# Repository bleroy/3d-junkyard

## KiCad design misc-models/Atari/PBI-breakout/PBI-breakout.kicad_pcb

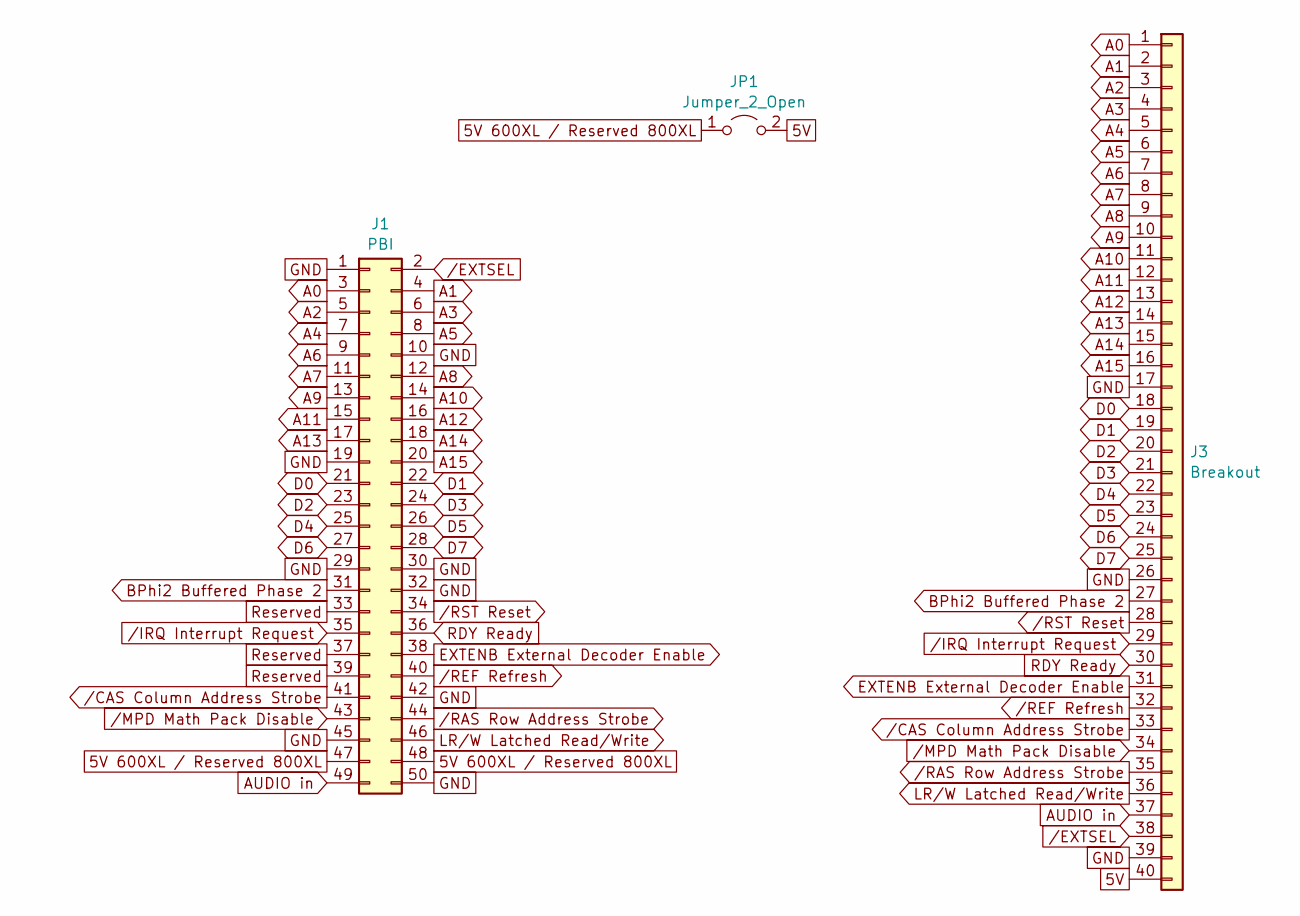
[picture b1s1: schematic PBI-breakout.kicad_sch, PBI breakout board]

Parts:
J1: PBI; PBI Edge Connector
J3: Breakout; PinHeader_1x40_P2.54mm_Horizontal
JP1: Jumper_2_Open; PinHeader_1x02_P2.54mm_Vertical

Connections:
5V: J3.40, JP1.2 (B)
5V 600XL / Reserved 800XL: J1.47, J1.48, JP1.1 (A)
A0: J1.3, J3.1
A1: J1.4, J3.2
A2: J1.5, J3.3
A3: J1.6, J3.4
A4: J1.7, J3.5
A5: J1.8, J3.6
A6: J1.9, J3.7
A7: J1.11, J3.8
A8: J1.12, J3.9
A9: J1.13, J3.10
A10: J1.14, J3.11
A11: J1.15, J3.12
A12: J1.16, J3.13
A13: J1.17, J3.14
A14: J1.18, J3.15
A15: J1.20, J3.16
AUDIO in: J1.49, J3.37
BPhi2 Buffered Phase 2: J1.31, J3.27
D0: J1.21, J3.18
D1: J1.22, J3.19
D2: J1.23, J3.20
D3: J1.24, J3.21
D4: J1.25, J3.22
D5: J1.26, J3.23
D6: J1.27, J3.24
D7: J1.28, J3.25
EXTENB External Decoder Enable: J1.38, J3.31
GND: J1.1, J1.10, J1.19, J1.29, J1.30, J1.32, J1.42, J1.45, J1.50, J3.17, J3.26, J3.39
LR/W Latched Read/Write: J1.46, J3.36
RDY Ready: J1.36, J3.30
Reserved: J1.33, J1.37, J1.39
/CAS Column Address Strobe: J1.41, J3.33
/EXTSEL: J1.2, J3.38
/IRQ Interrupt Request: J1.35, J3.29
/MPD Math Pack Disable: J1.43, J3.34
/RAS Row Address Strobe: J1.44, J3.35
/REF Refresh: J1.40, J3.32
/RST Reset: J1.34, J3.28

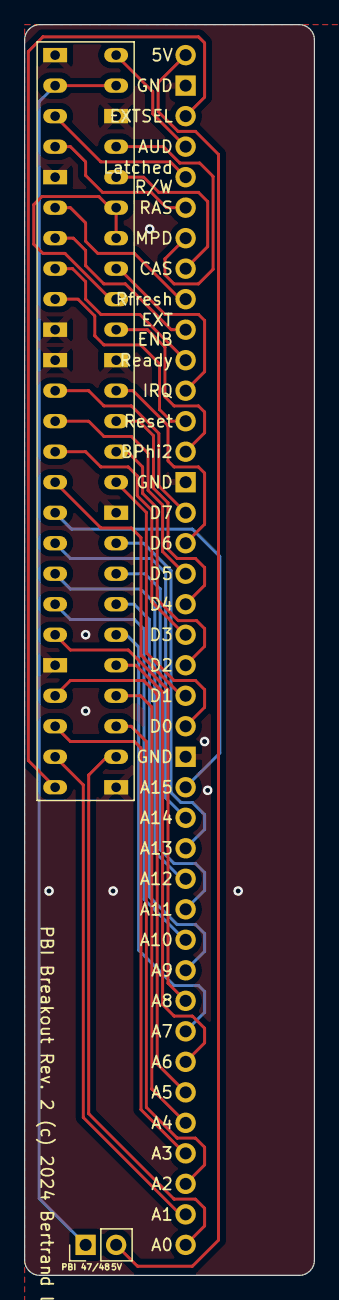
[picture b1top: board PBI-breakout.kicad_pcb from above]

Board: 2 copper layers, 24.1 x 104.1 mm, 3 parts (1 on the bottom side), 40 nets.

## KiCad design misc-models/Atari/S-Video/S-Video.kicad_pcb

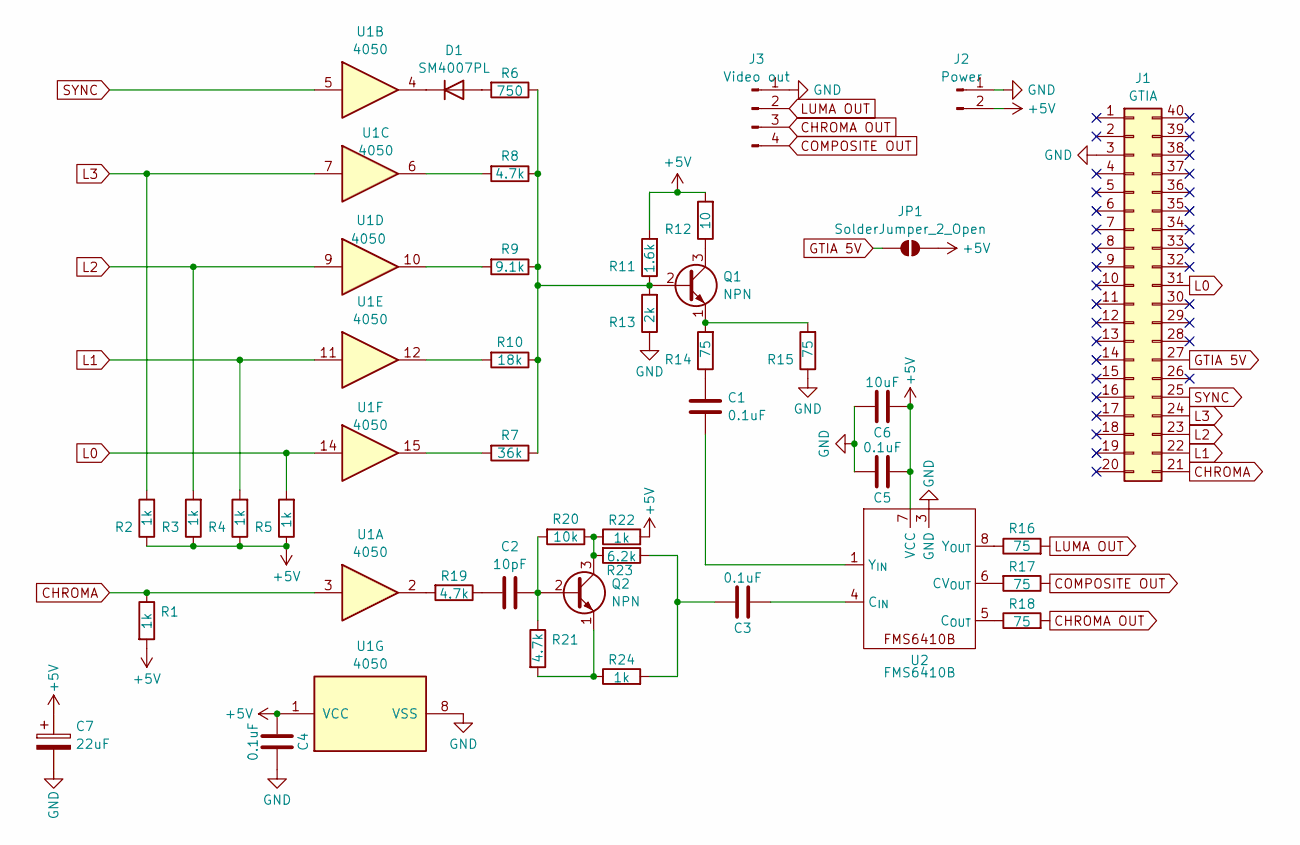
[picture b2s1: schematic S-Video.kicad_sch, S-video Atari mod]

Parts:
C1, C3, C4, C5: 0.1uF; C_0402_1005Metric; JLCPCB Part # C1525
C2: 10pF; C_0402_1005Metric; JLCPCB Part # C32949
C6: 10uF; C_0402_1005Metric; JLCPCB Part # C15525
C7: 22uF; C_Elec_4x5.4; JLCPCB Part # C98746
D1: SM4007PL; D_SOD-123; JLCPCB Part # C64898
J1: GTIA; DIP-40_W15.24mm_Socket
J2: Power; PinHeader_1x02_P2.54mm_Horizontal
J3: Video out; PinHeader_1x04_P2.54mm_Horizontal
JP1: SolderJumper_2_Open; SolderJumper-2_P1.3mm_Open_TrianglePad1.0x1.5mm
Q1, Q2: NPN; SOT-23; JLCPCB Part # C2145
R1, R2, R3, R4, R5, R22, R24: 1k; R_0402_1005Metric; JLCPCB Part # C11702
R6: 750; R_0402_1005Metric; JLCPCB Part # C25132
R7: 36k; R_0402_1005Metric; JLCPCB Part # C43676
R8, R19, R21: 4.7k; R_0402_1005Metric; JLCPCB Part # C25900
R9: 9.1k; R_0402_1005Metric; JLCPCB Part # C25926
R10: 18k; R_0402_1005Metric; JLCPCB Part # C25762
R11: 1.6k; R_0402_1005Metric; JLCPCB Part # C4908
R12: 10; R_0402_1005Metric; JLCPCB Part # C25077
R13: 2k; R_0402_1005Metric; JLCPCB Part # C4109
R14, R15, R16, R17, R18: 75; R_0402_1005Metric; JLCPCB Part # C25133
R20: 10k; R_0402_1005Metric; JLCPCB Part # C25744
R23: 6.2k; R_0402_1005Metric; JLCPCB Part # C137946
U1: 4050; SOIC-16_3.9x9.9mm_P1.27mm; JLCPCB Part # C131932
U2: FMS6410B; SOIC-8-1EP_3.9x4.9mm_P1.27mm_EP2.29x3mm; JLCPCB Part # C3823926

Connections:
+5V: C4.1, C5.1, C6.1, C7.1, J2.2, JP1.2 (B), R1.2, R2.1, R3.1, R4.1, R5.1, R11.2, R12.2, R22.2, U1.1 (VCC), U2.7 (VCC)
CHROMA: J1.21, R1.1, U1.3
CHROMA OUT: J3.3, R18.2
COMPOSITE OUT: J3.4, R17.1
GND: C4.2, C5.2, C6.2, C7.2, J1.3, J2.1, J3.1, R13.1, R15.1, U1.8 (VSS), U2.3 (GND)
GTIA 5V: J1.27, JP1.1 (A)
L0: J1.31, R5.2, U1.14
L1: J1.22, R4.2, U1.11
L2: J1.23, R3.2, U1.9
L3: J1.24, R2.2, U1.7
LUMA OUT: J3.2, R16.2
unnamed: C1.2, R14.1
unnamed: C2.2, R19.1
unnamed: C3.2, R23.1, R24.2
unnamed: D1.2 (A), R6.2
unnamed: D1.1 (K), U1.4
unnamed: Q1.2 (B), R6.1, R7.1, R8.1, R9.1, R10.1, R11.1, R13.2
unnamed: Q1.3 (C), R12.1
unnamed: Q1.1 (E), R14.2, R15.2
unnamed: C2.1, Q2.2 (B), R20.2, R21.1
unnamed: Q2.3 (C), R20.1, R22.1, R23.2
unnamed: Q2.1 (E), R21.2, R24.1
unnamed: R7.2, U1.15
unnamed: R8.2, U1.6
unnamed: R9.2, U1.10
unnamed: R10.2, U1.12
unnamed: R19.2, U1.2
unnamed: R17.2, U2.6 (CV_{OUT})
unnamed: C3.1, U2.4 (C_{IN})
unnamed: R18.1, U2.5 (C_{OUT})
unnamed: C1.1, U2.1 (Y_{IN})
unnamed: R16.1, U2.8 (Y_{OUT})
SYNC: J1.25, U1.5

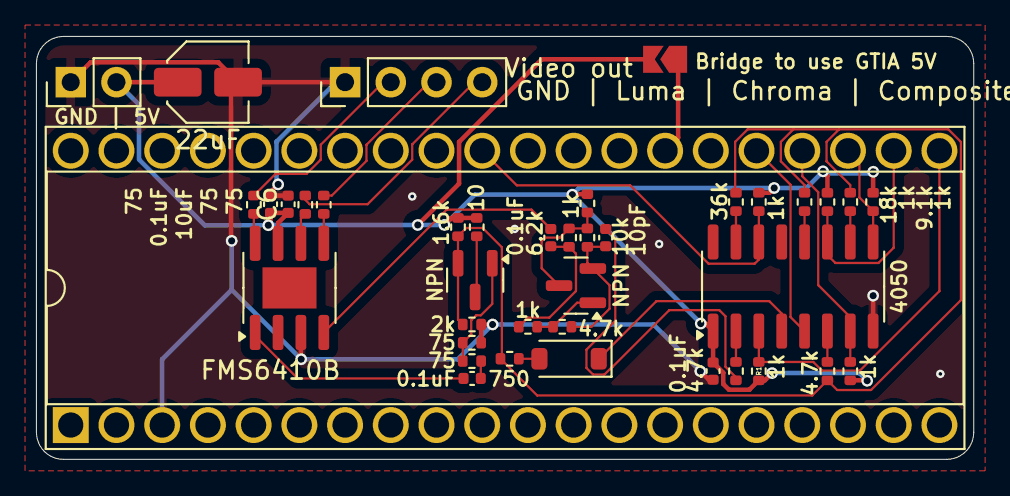
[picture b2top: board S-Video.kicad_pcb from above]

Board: 2 copper layers, 52.1 x 23.5 mm, 40 parts (0 on the bottom side), 33 nets.

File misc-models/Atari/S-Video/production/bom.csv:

Designator,Footprint,Quantity,Value,LCSC Part #
"C1, C3, C4, C5",0402,4,0.1uF,C1525
C2,0402,1,10pF,C32949
C6,0402,1,10uF,C15525
C7,C_Elec_4x5.4,1,22uF,C98746
D1,D_SOD-123,1,SM4007PL,C64898
J1,DIP-40_W15.24mm_Socket,1,GTIA,
J2,PinHeader_1x02_P2.54mm_Vertical,1,Power,
J3,PinHeader_1x04_P2.54mm_Vertical,1,Video out,
"Q1, Q2",SOT-23,2,NPN,C2145
"R1, R2, R22, R24, R3, R4, R5",0402,7,1k,C11702
R10,0402,1,18k,C25762
R11,0402,1,1.6k,C4908
R12,0402,1,10,C25077
R13,0402,1,2k,C4109
"R14, R15, R16, R17, R18",0402,5,75,C25133
"R19, R21, R8",0402,3,4.7k,C25900
R20,0402,1,10k,C25744
R23,0402,1,6.2k,C137946
R6,0402,1,750,C25132
R7,0402,1,36k,C43676
R9,0402,1,9.1k,C25926
U1,SOIC-16_3.9x9.9mm_P1.27mm,1,4050,C131932
U2,SOIC-8-1EP_3.9x4.9mm_P1.27mm_EP2.29x3mm,1,FMS6410B,C3823926

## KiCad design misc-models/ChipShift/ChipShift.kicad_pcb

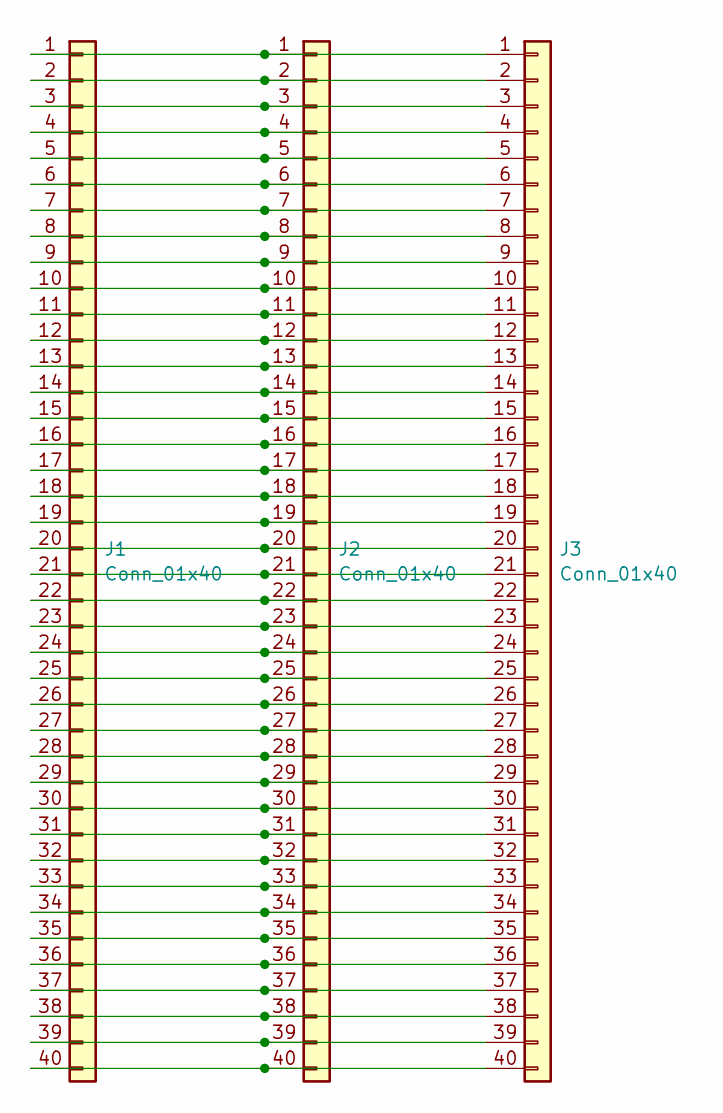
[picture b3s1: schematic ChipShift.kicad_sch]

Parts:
J1, J2: Conn_01x40; DIP-40_W25.4mm
J3: Conn_01x40; IDC-Header_2x20_P2.54mm_Vertical

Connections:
unnamed: J1.1, J2.1, J3.1
unnamed: J1.2, J2.2, J3.2
unnamed: J1.3, J2.3, J3.3
unnamed: J1.4, J2.4, J3.4
unnamed: J1.5, J2.5, J3.5
unnamed: J1.6, J2.6, J3.6
unnamed: J1.7, J2.7, J3.7
unnamed: J1.8, J2.8, J3.8
unnamed: J1.9, J2.9, J3.9
unnamed: J1.10, J2.10, J3.10
unnamed: J1.11, J2.11, J3.11
unnamed: J1.12, J2.12, J3.12
unnamed: J1.13, J2.13, J3.13
unnamed: J1.14, J2.14, J3.14
unnamed: J1.15, J2.15, J3.15
unnamed: J1.16, J2.16, J3.16
unnamed: J1.17, J2.17, J3.17
unnamed: J1.18, J2.18, J3.18
unnamed: J1.19, J2.19, J3.19
unnamed: J1.20, J2.20, J3.20
unnamed: J1.21, J2.21, J3.21
unnamed: J1.22, J2.22, J3.22
unnamed: J1.23, J2.23, J3.23
unnamed: J1.24, J2.24, J3.24
unnamed: J1.25, J2.25, J3.25
unnamed: J1.26, J2.26, J3.26
unnamed: J1.27, J2.27, J3.27
unnamed: J1.28, J2.28, J3.28
unnamed: J1.29, J2.29, J3.29
unnamed: J1.30, J2.30, J3.30
unnamed: J1.31, J2.31, J3.31
unnamed: J1.32, J2.32, J3.32
unnamed: J1.33, J2.33, J3.33
unnamed: J1.34, J2.34, J3.34
unnamed: J1.35, J2.35, J3.35
unnamed: J1.36, J2.36, J3.36
unnamed: J1.37, J2.37, J3.37
unnamed: J1.38, J2.38, J3.38
unnamed: J1.39, J2.39, J3.39
unnamed: J1.40, J2.40, J3.40

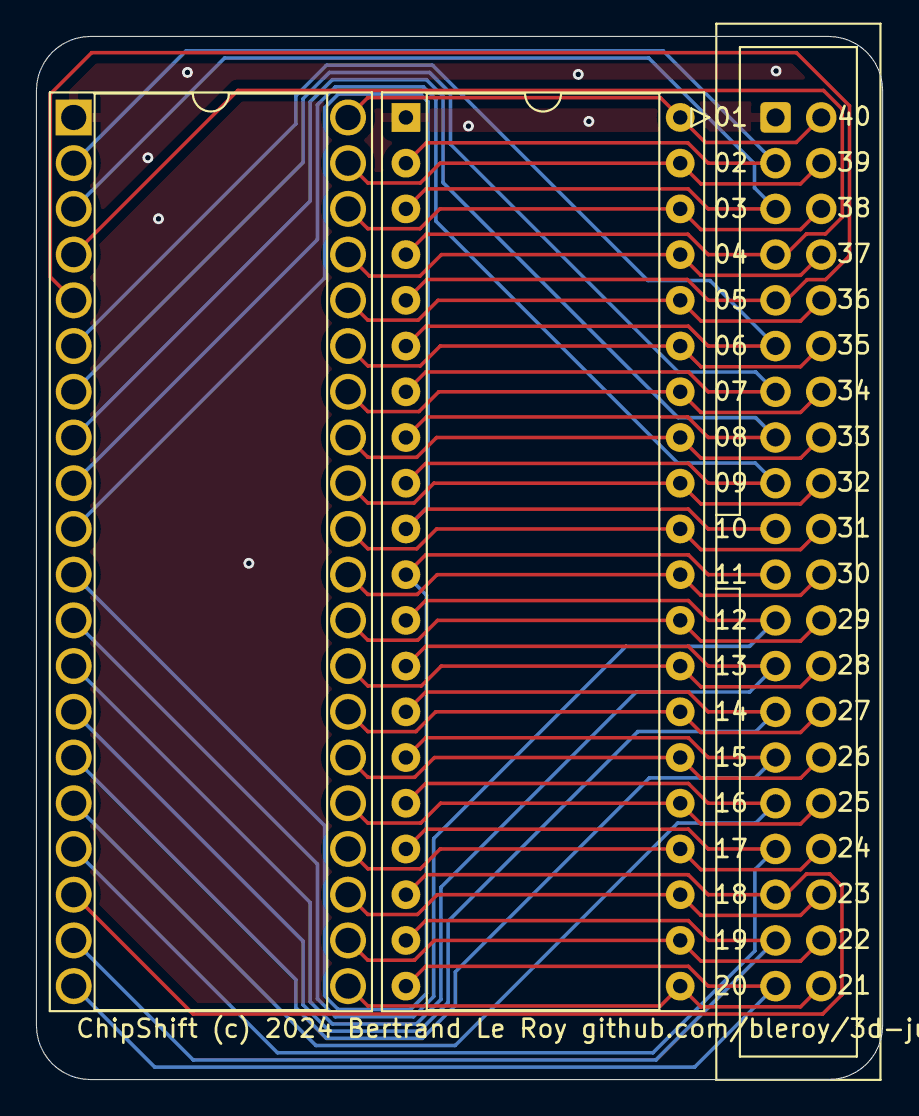
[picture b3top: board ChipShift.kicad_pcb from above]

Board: 2 copper layers, 47.0 x 58.0 mm, 3 parts (0 on the bottom side), 40 nets.

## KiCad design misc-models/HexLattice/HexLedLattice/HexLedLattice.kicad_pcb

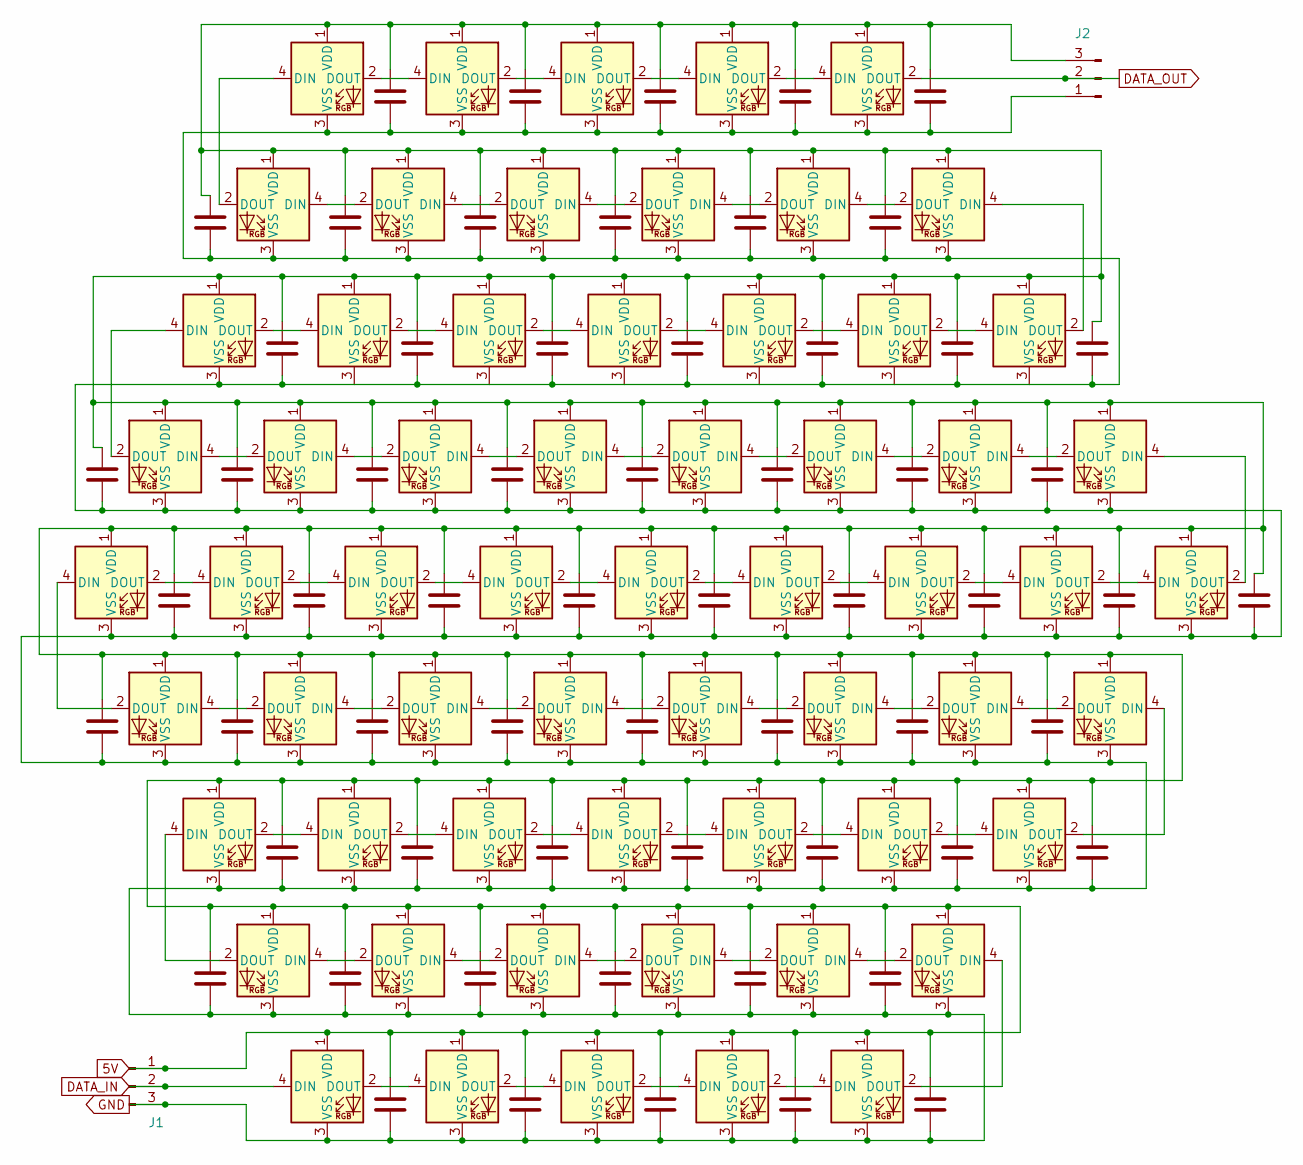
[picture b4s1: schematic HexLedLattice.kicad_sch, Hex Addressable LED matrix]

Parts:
C1, C2, C3, C4, C5, C6, C7, C8, C9, C10, C11, C12, C13, C14, C15, C16, C17, C18, C19, C20, C21, C22, C23, C24, C25, C26, C27, C28, C29, C30, C31, C32, C33, C34, C35, C36, C37, C38, C39, C40, C41, C42, C43, C44, C45, C46, C47, C48, C49, C50, C51, C52, C53, C54, C55, C56, C57, C58, C59, C60, C61: C; C_0201_0603Metric
D1, D2, D3, D4, D5, D6, D7, D8, D9, D10, D11, D12, D13, D14, D15, D16, D17, D18, D19, D20, D21, D22, D23, D24, D25, D26, D27, D28, D29, D30, D31, D32, D33, D34, D35, D36, D37, D38, D39, D40, D41, D42, D43, D44, D45, D46, D47, D48, D49, D50, D51, D52, D53, D54, D55, D56, D57, D58, D59, D60, D61: WS2812B; LED_WS2812B_PLCC4_5.0x5.0mm_P3.2mm
J1, J2: Conn_01x03_Pin; Connector_1x04-1MP_P1.0mm_Horizontal

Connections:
5V: C1.1, C2.1, C3.1, C4.1, C5.1, C6.1, C7.1, C8.1, C9.1, C10.1, C11.1, C12.1, C13.1, C14.1, C15.1, C16.1, C17.1, C18.1, C19.1, C20.1, C21.1, C22.1, C23.1, C24.1, C25.1, C26.1, C27.1, C28.1, C29.1, C30.1, C31.1, C32.1, C33.1, C34.1, C35.1, C36.1, C37.1, C38.1, C39.1, C40.1, C41.1, C42.1, C43.1, C44.1, C45.1, C46.1, C47.1, C48.1, C49.1, C50.1, C51.1, C52.1, C53.1, C54.1, C55.1, C56.1, C57.1, C58.1, C59.1, C60.1, C61.1, D1.1 (VDD), D2.1 (VDD), D3.1 (VDD), D4.1 (VDD), D5.1 (VDD), D6.1 (VDD), D7.1 (VDD), D8.1 (VDD), D9.1 (VDD), D10.1 (VDD), D11.1 (VDD), D12.1 (VDD), D13.1 (VDD), D14.1 (VDD), D15.1 (VDD), D16.1 (VDD), D17.1 (VDD), D18.1 (VDD), D19.1 (VDD), D20.1 (VDD), D21.1 (VDD), D22.1 (VDD), D23.1 (VDD), D24.1 (VDD), D25.1 (VDD), D26.1 (VDD), D27.1 (VDD), D28.1 (VDD), D29.1 (VDD), D30.1 (VDD), D31.1 (VDD), D32.1 (VDD), D33.1 (VDD), D34.1 (VDD), D35.1 (VDD), D36.1 (VDD), D37.1 (VDD), D38.1 (VDD), D39.1 (VDD), D40.1 (VDD), D41.1 (VDD), D42.1 (VDD), D43.1 (VDD), D44.1 (VDD), D45.1 (VDD), D46.1 (VDD), D47.1 (VDD), D48.1 (VDD), D49.1 (VDD), D50.1 (VDD), D51.1 (VDD), D52.1 (VDD), D53.1 (VDD), D54.1 (VDD), D55.1 (VDD), D56.1 (VDD), D57.1 (VDD), D58.1 (VDD), D59.1 (VDD), D60.1 (VDD), D61.1 (VDD), J1.1, J2.3
DATA_IN: D40.4 (DIN), J1.2
DATA_OUT: D5.2 (DOUT), J2.2
GND: C1.2, C2.2, C3.2, C4.2, C5.2, C6.2, C7.2, C8.2, C9.2, C10.2, C11.2, C12.2, C13.2, C14.2, C15.2, C16.2, C17.2, C18.2, C19.2, C20.2, C21.2, C22.2, C23.2, C24.2, C25.2, C26.2, C27.2, C28.2, C29.2, C30.2, C31.2, C32.2, C33.2, C34.2, C35.2, C36.2, C37.2, C38.2, C39.2, C40.2, C41.2, C42.2, C43.2, C44.2, C45.2, C46.2, C47.2, C48.2, C49.2, C50.2, C51.2, C52.2, C53.2, C54.2, C55.2, C56.2, C57.2, C58.2, C59.2, C60.2, C61.2, D1.3 (VSS), D2.3 (VSS), D3.3 (VSS), D4.3 (VSS), D5.3 (VSS), D6.3 (VSS), D7.3 (VSS), D8.3 (VSS), D9.3 (VSS), D10.3 (VSS), D11.3 (VSS), D12.3 (VSS), D13.3 (VSS), D14.3 (VSS), D15.3 (VSS), D16.3 (VSS), D17.3 (VSS), D18.3 (VSS), D19.3 (VSS), D20.3 (VSS), D21.3 (VSS), D22.3 (VSS), D23.3 (VSS), D24.3 (VSS), D25.3 (VSS), D26.3 (VSS), D27.3 (VSS), D28.3 (VSS), D29.3 (VSS), D30.3 (VSS), D31.3 (VSS), D32.3 (VSS), D33.3 (VSS), D34.3 (VSS), D35.3 (VSS), D36.3 (VSS), D37.3 (VSS), D38.3 (VSS), D39.3 (VSS), D40.3 (VSS), D41.3 (VSS), D42.3 (VSS), D43.3 (VSS), D44.3 (VSS), D45.3 (VSS), D46.3 (VSS), D47.3 (VSS), D48.3 (VSS), D49.3 (VSS), D50.3 (VSS), D51.3 (VSS), D52.3 (VSS), D53.3 (VSS), D54.3 (VSS), D55.3 (VSS), D56.3 (VSS), D57.3 (VSS), D58.3 (VSS), D59.3 (VSS), D60.3 (VSS), D61.3 (VSS), J1.3, J2.1
unnamed: D1.4 (DIN), D11.2 (DOUT)
unnamed: D1.2 (DOUT), D2.4 (DIN)
unnamed: D2.2 (DOUT), D3.4 (DIN)
unnamed: D3.2 (DOUT), D4.4 (DIN)
unnamed: D4.2 (DOUT), D5.4 (DIN)
unnamed: D6.2 (DOUT), D7.4 (DIN)
unnamed: D7.2 (DOUT), D8.4 (DIN)
unnamed: D8.2 (DOUT), D9.4 (DIN)
unnamed: D9.2 (DOUT), D10.4 (DIN)
unnamed: D10.2 (DOUT), D11.4 (DIN)
unnamed: D12.4 (DIN), D26.2 (DOUT)
unnamed: D12.2 (DOUT), D13.4 (DIN)
unnamed: D13.2 (DOUT), D14.4 (DIN)
unnamed: D14.2 (DOUT), D15.4 (DIN)
unnamed: D15.2 (DOUT), D16.4 (DIN)
unnamed: D16.2 (DOUT), D17.4 (DIN)
unnamed: D17.2 (DOUT), D18.4 (DIN)
unnamed: D6.4 (DIN), D18.2 (DOUT)
unnamed: D19.4 (DIN), D52.2 (DOUT)
unnamed: D19.2 (DOUT), D20.4 (DIN)
unnamed: D20.2 (DOUT), D21.4 (DIN)
unnamed: D21.2 (DOUT), D22.4 (DIN)
unnamed: D22.2 (DOUT), D23.4 (DIN)
unnamed: D23.2 (DOUT), D24.4 (DIN)
unnamed: D24.2 (DOUT), D25.4 (DIN)
unnamed: D25.2 (DOUT), D26.4 (DIN)
unnamed: D27.4 (DIN), D39.2 (DOUT)
unnamed: D27.2 (DOUT), D28.4 (DIN)
unnamed: D28.2 (DOUT), D29.4 (DIN)
unnamed: D29.2 (DOUT), D30.4 (DIN)
unnamed: D30.2 (DOUT), D31.4 (DIN)
unnamed: D31.2 (DOUT), D32.4 (DIN)
unnamed: D32.2 (DOUT), D33.4 (DIN)
unnamed: D33.2 (DOUT), D54.4 (DIN)
unnamed: D34.4 (DIN), D44.2 (DOUT)
unnamed: D34.2 (DOUT), D35.4 (DIN)
unnamed: D35.2 (DOUT), D36.4 (DIN)
unnamed: D36.2 (DOUT), D37.4 (DIN)
unnamed: D37.2 (DOUT), D38.4 (DIN)
unnamed: D38.2 (DOUT), D39.4 (DIN)
unnamed: D40.2 (DOUT), D41.4 (DIN)
unnamed: D41.2 (DOUT), D42.4 (DIN)
unnamed: D42.2 (DOUT), D43.4 (DIN)
unnamed: D43.2 (DOUT), D44.4 (DIN)
unnamed: D45.4 (DIN), D53.2 (DOUT)
unnamed: D45.2 (DOUT), D46.4 (DIN)
unnamed: D46.2 (DOUT), D47.4 (DIN)
unnamed: D47.2 (DOUT), D48.4 (DIN)
unnamed: D48.2 (DOUT), D49.4 (DIN)
unnamed: D49.2 (DOUT), D50.4 (DIN)
unnamed: D50.2 (DOUT), D51.4 (DIN)
unnamed: D51.2 (DOUT), D52.4 (DIN)
unnamed: D53.4 (DIN), D61.2 (DOUT)
unnamed: D54.2 (DOUT), D55.4 (DIN)
unnamed: D55.2 (DOUT), D56.4 (DIN)
unnamed: D56.2 (DOUT), D57.4 (DIN)
unnamed: D57.2 (DOUT), D58.4 (DIN)
unnamed: D58.2 (DOUT), D59.4 (DIN)
unnamed: D59.2 (DOUT), D60.4 (DIN)
unnamed: D60.2 (DOUT), D61.4 (DIN)

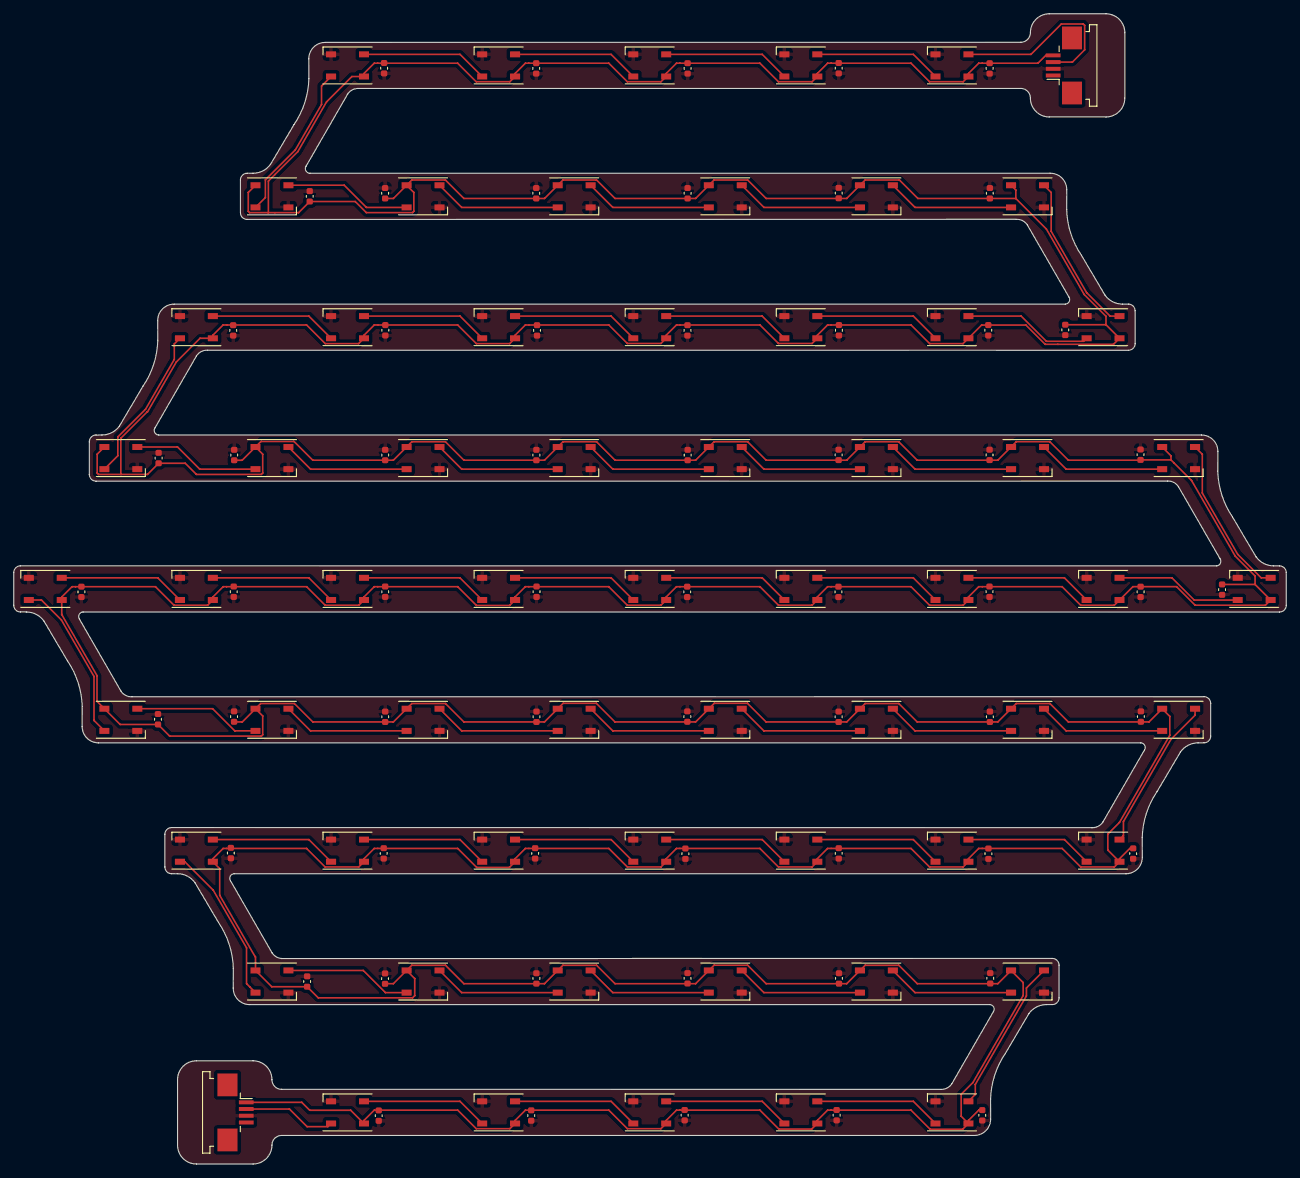
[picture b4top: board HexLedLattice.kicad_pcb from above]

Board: 2 copper layers, 189.5 x 171.3 mm, 124 parts (0 on the bottom side), 64 nets.

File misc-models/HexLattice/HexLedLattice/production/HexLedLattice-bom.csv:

Designator,Footprint,Quantity,Value,LCSC Part #
"C1, C10, C11, C12, C13, C14, C15, C16, C17, C18, C19, C2, C20, C21, C22, C23, C24, C25, C26, C27, C28, C29, C3, C30, C31, C32, C33, C34, C35, C36, C37, C38, C39, C4, C40, C41, C42, C43, C44, C45, C46, C47, C48, C49, C5, C50, C51, C52, C53, C54, C55, C56, C57, C58, C59, C6, C60, C61, C7, C8, C9",0603,61,C,
"D1, D10, D11, D12, D13, D14, D15, D16, D17, D18, D19, D2, D20, D21, D22, D23, D24, D25, D26, D27, D28, D29, D3, D30, D31, D32, D33, D34, D35, D36, D37, D38, D39, D4, D40, D41, D42, D43, D44, D45, D46, D47, D48, D49, D5, D50, D51, D52, D53, D54, D55, D56, D57, D58, D59, D6, D60, D61, D7, D8, D9",LED_WS2812B_PLCC4_5.0x5.0mm_P3.2mm,61,WS2812B,
"J1, J2",Connector_1x04-1MP_P1.0mm_Horizontal,2,Conn_01x03_Pin,

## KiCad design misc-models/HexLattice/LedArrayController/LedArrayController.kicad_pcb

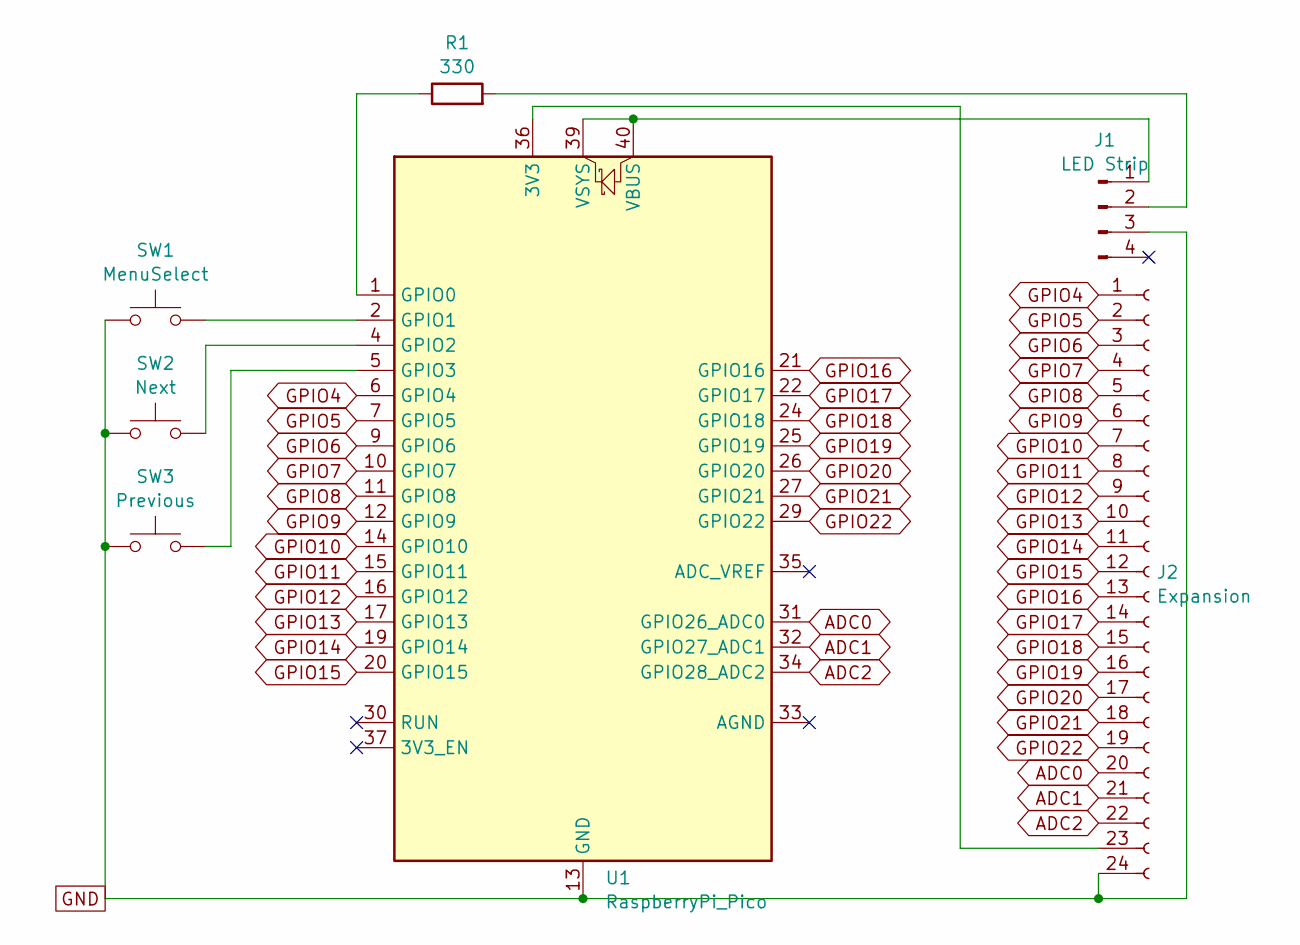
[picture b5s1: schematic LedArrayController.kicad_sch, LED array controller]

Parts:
J1: LED Strip; Connector_1x04-1MP_P1.0mm_Horizontal
J2: Expansion; PinSocket_1x24_P2.54mm_Horizontal
R1: 330; R_Axial_DIN0207_L6.3mm_D2.5mm_P7.62mm_Horizontal
SW1: MenuSelect; SW_PUSH_6mm
SW2: Next; SW_PUSH_6mm
SW3: Previous; SW_PUSH_6mm
U1: RaspberryPi_Pico; RaspberryPi_Pico_W_SMD_MountingHoles_Castellated_HandSolder

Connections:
ADC0: J2.20, U1.31 (GPIO26_ADC0)
ADC1: J2.21, U1.32 (GPIO27_ADC1)
ADC2: J2.22, U1.34 (GPIO28_ADC2)
GND: J1.3, J2.24, SW1.1, SW2.1, SW3.1, U1.3 (GND), U1.8 (GND), U1.13 (GND), U1.18 (GND), U1.23 (GND), U1.28 (GND), U1.38 (GND)
GPIO4: J2.1, U1.6 (GPIO4)
GPIO5: J2.2, U1.7 (GPIO5)
GPIO6: J2.3, U1.9 (GPIO6)
GPIO7: J2.4, U1.10 (GPIO7)
GPIO8: J2.5, U1.11 (GPIO8)
GPIO9: J2.6, U1.12 (GPIO9)
GPIO10: J2.7, U1.14 (GPIO10)
GPIO11: J2.8, U1.15 (GPIO11)
GPIO12: J2.9, U1.16 (GPIO12)
GPIO13: J2.10, U1.17 (GPIO13)
GPIO14: J2.11, U1.19 (GPIO14)
GPIO15: J2.12, U1.20 (GPIO15)
GPIO16: J2.13, U1.21 (GPIO16)
GPIO17: J2.14, U1.22 (GPIO17)
GPIO18: J2.15, U1.24 (GPIO18)
GPIO19: J2.16, U1.25 (GPIO19)
GPIO20: J2.17, U1.26 (GPIO20)
GPIO21: J2.18, U1.27 (GPIO21)
GPIO22: J2.19, U1.29 (GPIO22)
unnamed: J1.1, U1.39 (VSYS), U1.40 (VBUS)
unnamed: J1.2, R1.2
unnamed: J2.23, U1.36 (3V3)
unnamed: R1.1, U1.1 (GPIO0)
unnamed: SW1.2, U1.2 (GPIO1)
unnamed: SW2.2, U1.4 (GPIO2)
unnamed: SW3.2, U1.5 (GPIO3)

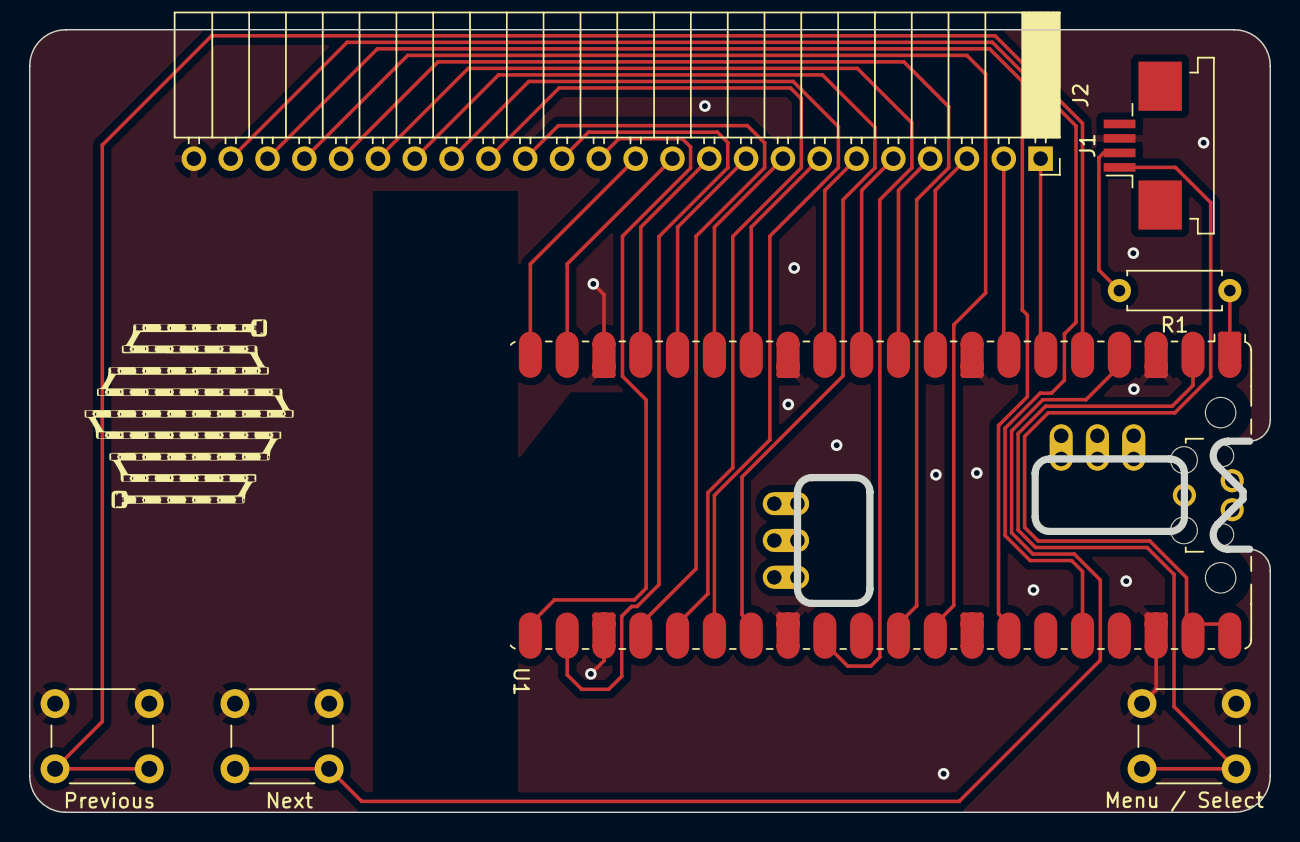
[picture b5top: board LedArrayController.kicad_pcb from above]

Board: 2 copper layers, 85.6 x 54.0 mm, 7 parts (0 on the bottom side), 30 nets.

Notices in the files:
misc-models/Atari/PBI-breakout/PBI-breakout.kicad_pcb:
PBI Breakout Rev. 2 (c) 2024 Bertrand Le Roy
misc-models/ChipShift/ChipShift.kicad_pcb:
ChipShift (c) 2024 Bertrand Le Roy github.com/bleroy/3d-junkyard
